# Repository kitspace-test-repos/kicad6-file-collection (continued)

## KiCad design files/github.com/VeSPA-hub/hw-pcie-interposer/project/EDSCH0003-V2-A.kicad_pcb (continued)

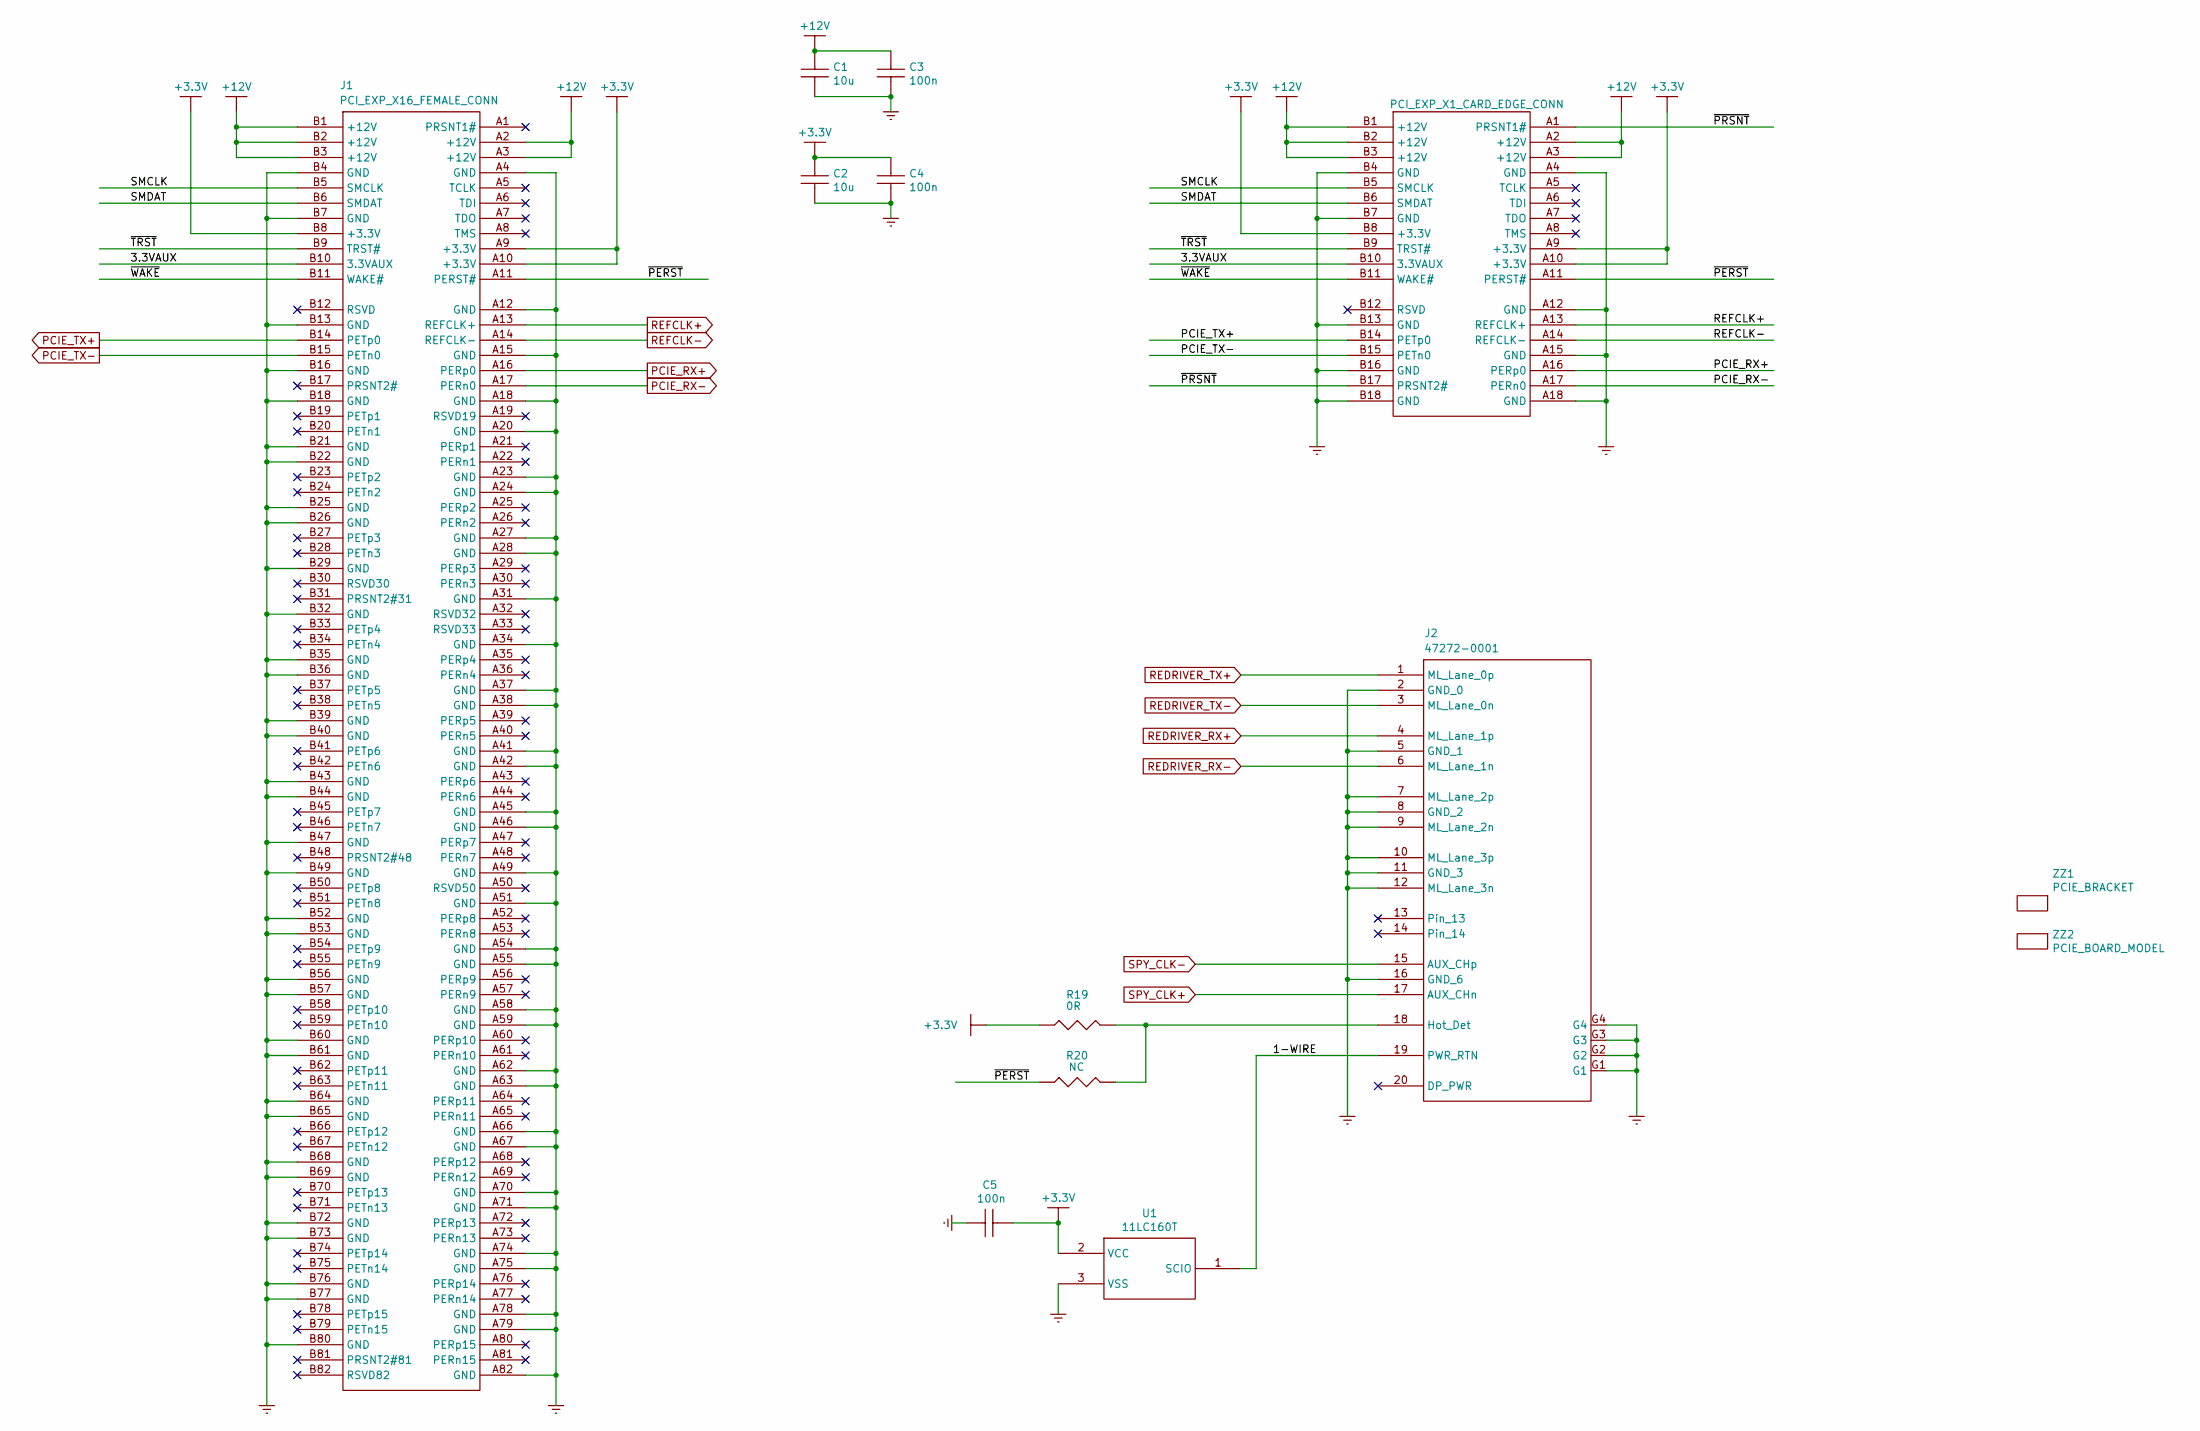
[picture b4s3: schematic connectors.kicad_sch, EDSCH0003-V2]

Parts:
C1, C2: C10U_50V_1206; c_smt1206_ref
C3, C4, C5: C100N_16V_0402; r_smt0402_ref
J1: PCIEXP_X16_EDGE_MOUNT_CONN; samtec_pcie_ems2
J2: DISPLAY_PORT; molex_display_port
P1: PCIEXP_X1_CARD_EDGE; BUS_PCIexpress_x1
R19: R0R_5%_0402; r_smt0402_ref
R20: R_NC_0402; r_smt0402_ref
U1: EEPROM_1WIRE_2Kx8_11LC160T; SOT-23
ZZ1: PCIE_BRACKET; pcie_bracket
ZZ2: PCIE_BOARD_MODEL; BUS_PCIexpress

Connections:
+3.3V: C2.1, C4.1, C5.2, J1.A9 (+3.3V), J1.A10 (+3.3V), J1.B8 (+3.3V), P1.A9 (+3.3V), P1.A10 (+3.3V), P1.B8 (+3.3V), R19.1, U1.2 (VCC); also elsewhere on the board
+12V: C1.1, C3.1, J1.A2 (+12V), J1.A3 (+12V), J1.B1 (+12V), J1.B2 (+12V), J1.B3 (+12V), P1.A2 (+12V), P1.A3 (+12V), P1.B1 (+12V), P1.B2 (+12V), P1.B3 (+12V)
/MASTER_SHEET/CONNECTORS/1-WIRE: J2.19 (PWR_RTN), U1.1 (SCIO)
/MASTER_SHEET/CONNECTORS/3.3VAUX: J1.B10 (3.3VAUX), P1.B10 (3.3VAUX)
/MASTER_SHEET/CONNECTORS/SMCLK: J1.B5 (SMCLK), P1.B5 (SMCLK)
/MASTER_SHEET/CONNECTORS/SMDAT: J1.B6 (SMDAT), P1.B6 (SMDAT)
/MASTER_SHEET/CONNECTORS/~PERST: J1.A11 (PERST#), P1.A11 (PERST#), R20.1
/MASTER_SHEET/CONNECTORS/~PRSNT: P1.A1 (PRSNT1#), P1.B17 (PRSNT2#)
/MASTER_SHEET/CONNECTORS/~TRST: J1.B9 (TRST#), P1.B9 (TRST#)
/MASTER_SHEET/CONNECTORS/~WAKE: J1.B11 (WAKE#), P1.B11 (WAKE#)
GND: C1.2, C2.2, C3.2, C4.2, C5.1, J1.A4 (GND), J1.A12 (GND), J1.A15 (GND), J1.A18 (GND), J1.A20 (GND), J1.A23 (GND), J1.A24 (GND), J1.A27 (GND), J1.A28 (GND), J1.A31 (GND), J1.A34 (GND), J1.A37 (GND), J1.A38 (GND), J1.A41 (GND), J1.A42 (GND), J1.A45 (GND), J1.A46 (GND), J1.A49 (GND), J1.A51 (GND), J1.A54 (GND), J1.A55 (GND), J1.A58 (GND), J1.A59 (GND), J1.A62 (GND), J1.A63 (GND), J1.A66 (GND), J1.A67 (GND), J1.A70 (GND), J1.A71 (GND), J1.A74 (GND), J1.A75 (GND), J1.A78 (GND), J1.A79 (GND), J1.A82 (GND), J1.B4 (GND), J1.B7 (GND), J1.B13 (GND), J1.B16 (GND), J1.B18 (GND), J1.B21 (GND), J1.B22 (GND), J1.B25 (GND), J1.B26 (GND), J1.B29 (GND), J1.B32 (GND), J1.B35 (GND), J1.B36 (GND), J1.B39 (GND), J1.B40 (GND), J1.B43 (GND), J1.B44 (GND), J1.B47 (GND), J1.B49 (GND), J1.B52 (GND), J1.B53 (GND), J1.B56 (GND), J1.B57 (GND), J1.B60 (GND), J1.B61 (GND), J1.B64 (GND), J1.B65 (GND), J1.B68 (GND), J1.B69 (GND), J1.B72 (GND), J1.B73 (GND), J1.B76 (GND), J1.B77 (GND), J1.B80 (GND), J2.2 (GND_0), J2.5 (GND_1), J2.7 (ML_Lane_2p), J2.8 (GND_2), J2.9 (ML_Lane_2n), J2.10 (ML_Lane_3p), J2.11 (GND_3), J2.12 (ML_Lane_3n), J2.16 (GND_6), J2.G1, J2.G2, J2.G3, J2.G4, P1.A4 (GND), P1.A12 (GND), P1.A15 (GND), P1.A18 (GND), P1.B4 (GND), P1.B7 (GND), P1.B13 (GND), P1.B16 (GND), P1.B18 (GND), U1.3 (VSS); also elsewhere on the board
unnamed: J2.18 (Hot_Det), R19.2, R20.2
PCIE_RX+: J1.A16 (PERp0), P1.A16 (PERp0); also elsewhere on the board
PCIE_RX-: J1.A17 (PERn0), P1.A17 (PERn0); also elsewhere on the board
PCIE_TX+: J1.B14 (PETp0), P1.B14 (PETp0); also elsewhere on the board
PCIE_TX-: J1.B15 (PETn0), P1.B15 (PETn0); also elsewhere on the board
REDRIVER_RX+: J2.4 (ML_Lane_1p); also elsewhere on the board
REDRIVER_RX-: J2.6 (ML_Lane_1n); also elsewhere on the board
REDRIVER_TX+: J2.1 (ML_Lane_0p); also elsewhere on the board
REDRIVER_TX-: J2.3 (ML_Lane_0n); also elsewhere on the board
REFCLK+: J1.A13 (REFCLK+), P1.A13 (REFCLK+); also elsewhere on the board
REFCLK-: J1.A14 (REFCLK-), P1.A14 (REFCLK-); also elsewhere on the board
SPY_CLK+: J2.17 (AUX_CHn); also elsewhere on the board
SPY_CLK-: J2.15 (AUX_CHp); also elsewhere on the board

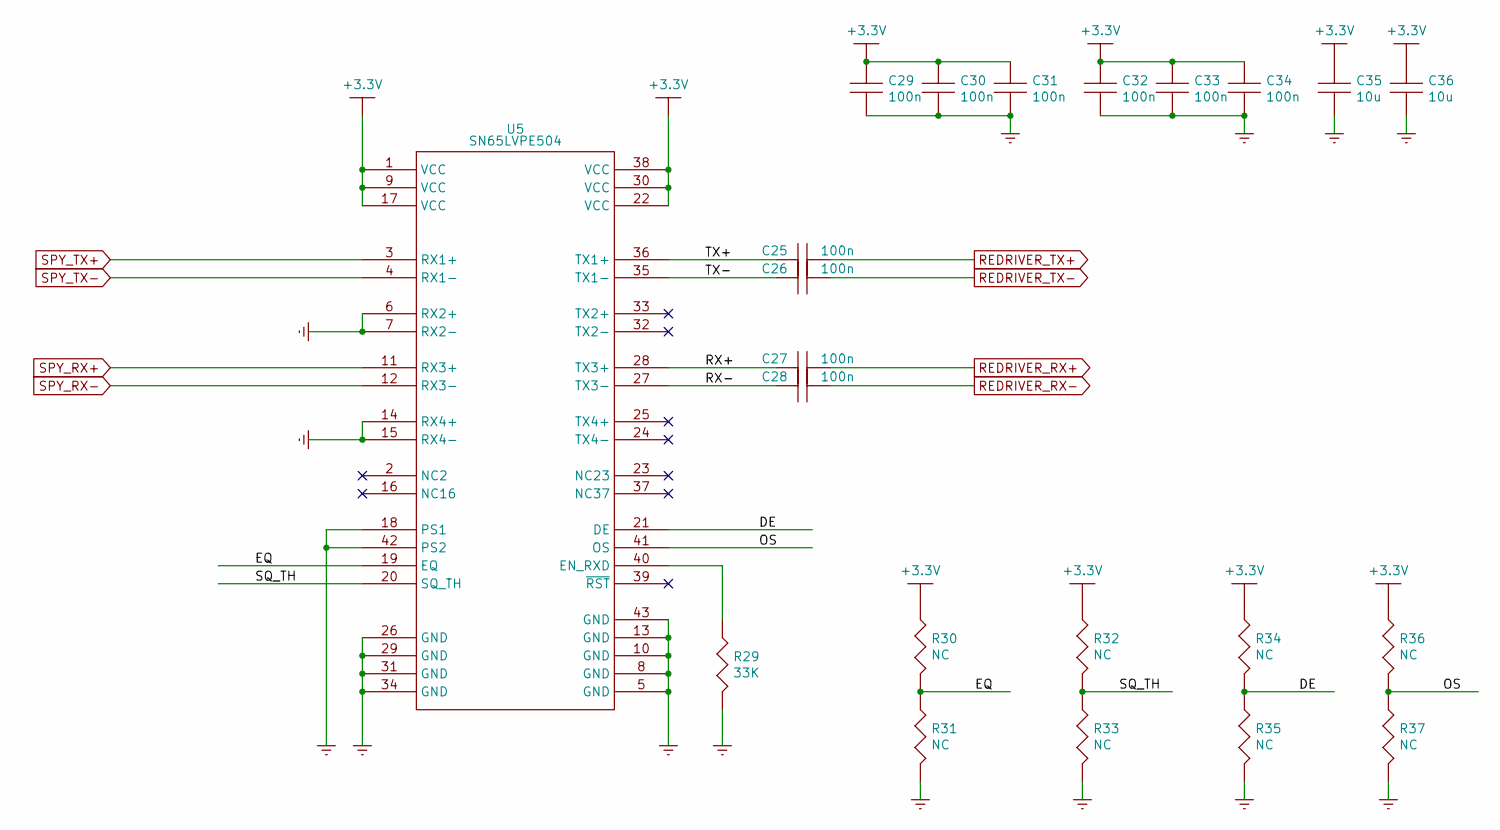
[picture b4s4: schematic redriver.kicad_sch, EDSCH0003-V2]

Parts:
C25, C26, C27, C28, C29, C30, C31, C32, C33, C34: C100N_16V_0402; r_smt0402_ref
C35, C36: C10U_50V_1206; c_smt1206_ref
R29: R33K_1%_0402; r_smt0402_ref
R30, R31, R32, R33, R34, R35, R36, R37: R_NC_0402; r_smt0402_ref
U5: PCIe_HALF_x4_Gen2_SN65LVPE504; pwqfn-n42

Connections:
+3.3V: C29.1, C30.1, C31.1, C32.1, C33.1, C34.1, C35.1, C36.1, R30.1, R32.1, R34.1, R36.1, U5.1 (VCC), U5.9 (VCC), U5.17 (VCC), U5.22 (VCC), U5.30 (VCC), U5.38 (VCC); also elsewhere on the board
/MASTER_SHEET/REDRIVER/DE: R34.2, R35.1, U5.21 (DE)
/MASTER_SHEET/REDRIVER/EQ: R30.2, R31.1, U5.19 (EQ)
/MASTER_SHEET/REDRIVER/OS: R36.2, R37.1, U5.41 (OS)
/MASTER_SHEET/REDRIVER/RX+: C27.1, U5.28 (TX3+)
/MASTER_SHEET/REDRIVER/RX-: C28.1, U5.27 (TX3-)
/MASTER_SHEET/REDRIVER/SQ_TH: R32.2, R33.1, U5.20 (SQ_TH)
/MASTER_SHEET/REDRIVER/TX+: C25.1, U5.36 (TX1+)
/MASTER_SHEET/REDRIVER/TX-: C26.1, U5.35 (TX1-)
GND: C29.2, C30.2, C31.2, C32.2, C33.2, C34.2, C35.2, C36.2, R29.2, R31.2, R33.2, R35.2, R37.2, U5.5 (GND), U5.6 (RX2+), U5.7 (RX2-), U5.8 (GND), U5.10 (GND), U5.13 (GND), U5.14 (RX4+), U5.15 (RX4-), U5.18 (PS1), U5.26 (GND), U5.29 (GND), U5.31 (GND), U5.34 (GND), U5.42 (PS2), U5.43 (GND); also elsewhere on the board
unnamed: R29.1, U5.40 (EN_RXD)
REDRIVER_RX+: C27.2; also elsewhere on the board
REDRIVER_RX-: C28.2; also elsewhere on the board
REDRIVER_TX+: C25.2; also elsewhere on the board
REDRIVER_TX-: C26.2; also elsewhere on the board
SPY_RX+: U5.11 (RX3+); also elsewhere on the board
SPY_RX-: U5.12 (RX3-); also elsewhere on the board
SPY_TX+: U5.3 (RX1+); also elsewhere on the board
SPY_TX-: U5.4 (RX1-); also elsewhere on the board

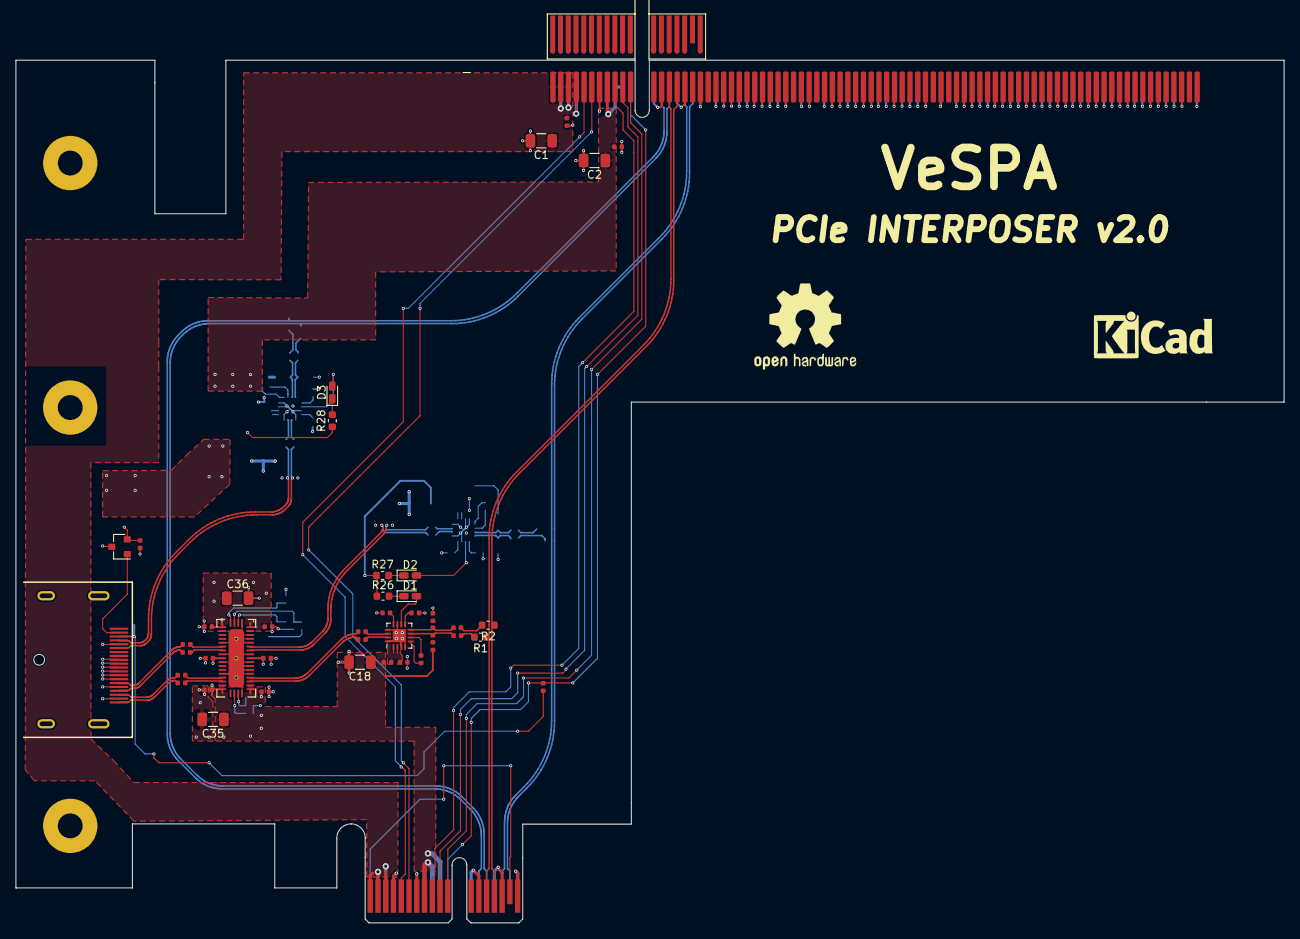
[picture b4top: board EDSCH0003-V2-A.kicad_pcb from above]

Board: 4 copper layers, 163.4 x 111.2 mm, 89 parts (0 on the bottom side), 76 nets.

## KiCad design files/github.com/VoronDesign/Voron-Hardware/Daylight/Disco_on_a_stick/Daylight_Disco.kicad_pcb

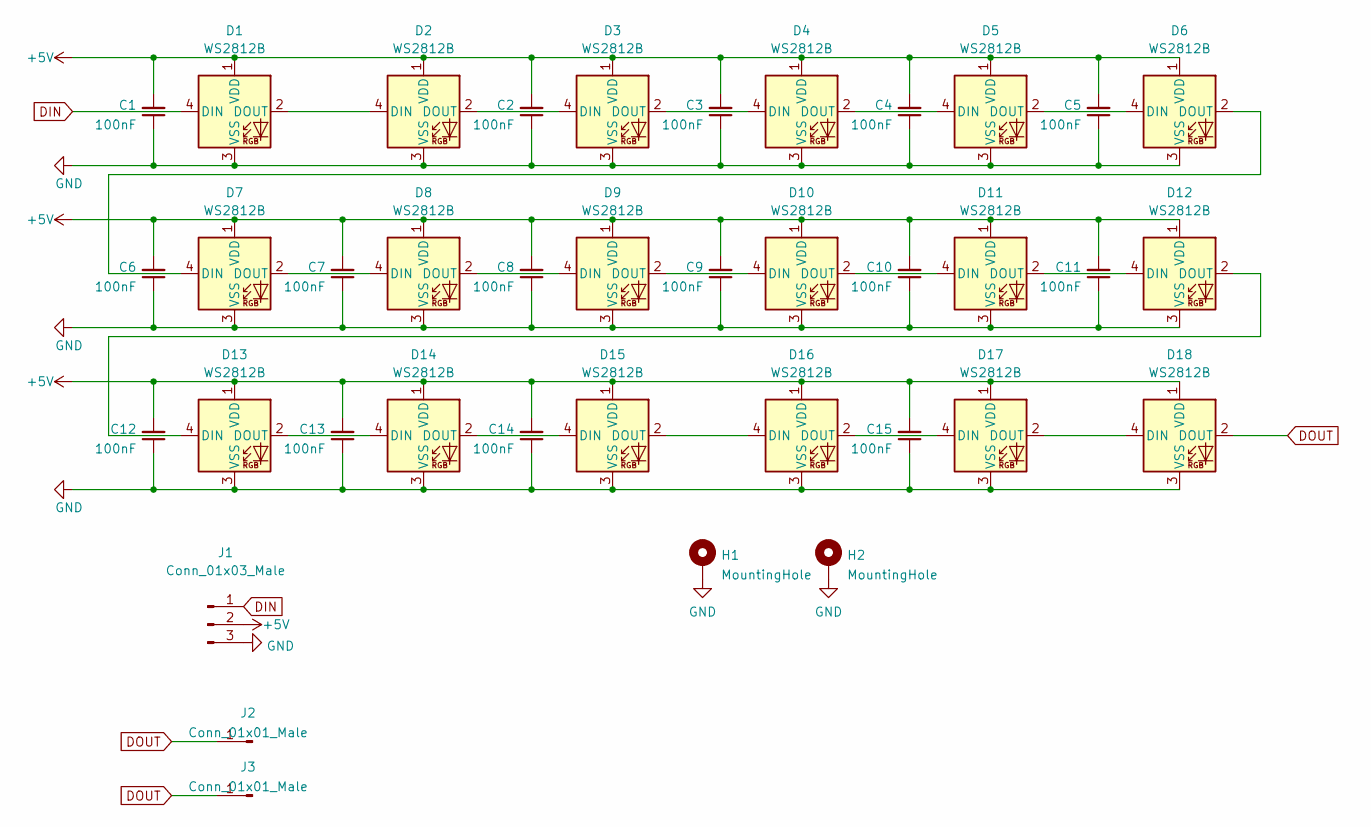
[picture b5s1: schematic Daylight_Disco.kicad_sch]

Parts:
C1, C2, C3, C4, C5, C6, C7, C8, C9, C10, C11, C12, C13, C14, C15: 100nF; C_0805_2012Metric_Pad1.18x1.45mm_HandSolder
D1, D2, D3, D4, D5, D6, D7, D8, D9, D10, D11, D12, D13, D14, D15, D16, D17, D18: WS2812B; LED_WS2812B_PLCC4_5.0x5.0mm_P3.2mm
H1, H2: MountingHole; MountingHole_3.2mm_M3_Pad_Via
J1: Conn_01x03_Male; JST_XH_S3B-XH-A-1_1x03_P2.50mm_Horizontal
J2, J3: Conn_01x01_Male; PinHeader-1-with-SMDpad

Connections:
+5V: C1.2, C2.2, C3.2, C4.2, C5.2, C6.2, C7.2, C8.2, C9.2, C10.2, C11.2, C12.2, C13.2, C14.2, C15.2, D1.1 (VDD), D2.1 (VDD), D3.1 (VDD), D4.1 (VDD), D5.1 (VDD), D6.1 (VDD), D7.1 (VDD), D8.1 (VDD), D9.1 (VDD), D10.1 (VDD), D11.1 (VDD), D12.1 (VDD), D13.1 (VDD), D14.1 (VDD), D15.1 (VDD), D16.1 (VDD), D17.1 (VDD), D18.1 (VDD), J1.2
DIN: D1.4 (DIN), J1.1
DOUT: D18.2 (DOUT), J2.1, J3.1
GND: C1.1, C2.1, C3.1, C4.1, C5.1, C6.1, C7.1, C8.1, C9.1, C10.1, C11.1, C12.1, C13.1, C14.1, C15.1, D1.3 (VSS), D2.3 (VSS), D3.3 (VSS), D4.3 (VSS), D5.3 (VSS), D6.3 (VSS), D7.3 (VSS), D8.3 (VSS), D9.3 (VSS), D10.3 (VSS), D11.3 (VSS), D12.3 (VSS), D13.3 (VSS), D14.3 (VSS), D15.3 (VSS), D16.3 (VSS), D17.3 (VSS), D18.3 (VSS), H1.1, H2.1, J1.3
unnamed: D1.2 (DOUT), D2.4 (DIN)
unnamed: D2.2 (DOUT), D3.4 (DIN)
unnamed: D3.2 (DOUT), D4.4 (DIN)
unnamed: D4.2 (DOUT), D5.4 (DIN)
unnamed: D5.2 (DOUT), D6.4 (DIN)
unnamed: D6.2 (DOUT), D7.4 (DIN)
unnamed: D7.2 (DOUT), D8.4 (DIN)
unnamed: D8.2 (DOUT), D9.4 (DIN)
unnamed: D10.2 (DOUT), D11.4 (DIN)
unnamed: D9.2 (DOUT), D10.4 (DIN)
unnamed: D11.2 (DOUT), D12.4 (DIN)
unnamed: D12.2 (DOUT), D13.4 (DIN)
unnamed: D13.2 (DOUT), D14.4 (DIN)
unnamed: D14.2 (DOUT), D15.4 (DIN)
unnamed: D15.2 (DOUT), D16.4 (DIN)
unnamed: D16.2 (DOUT), D17.4 (DIN)
unnamed: D17.2 (DOUT), D18.4 (DIN)

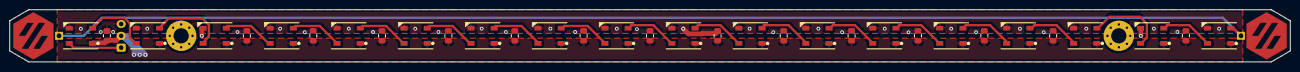
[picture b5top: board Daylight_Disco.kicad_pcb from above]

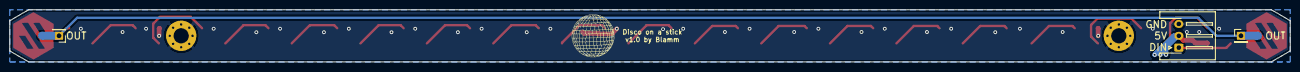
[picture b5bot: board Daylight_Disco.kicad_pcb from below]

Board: 2 copper layers, 270.0 x 11.0 mm, 38 parts (3 on the bottom side), 21 nets.

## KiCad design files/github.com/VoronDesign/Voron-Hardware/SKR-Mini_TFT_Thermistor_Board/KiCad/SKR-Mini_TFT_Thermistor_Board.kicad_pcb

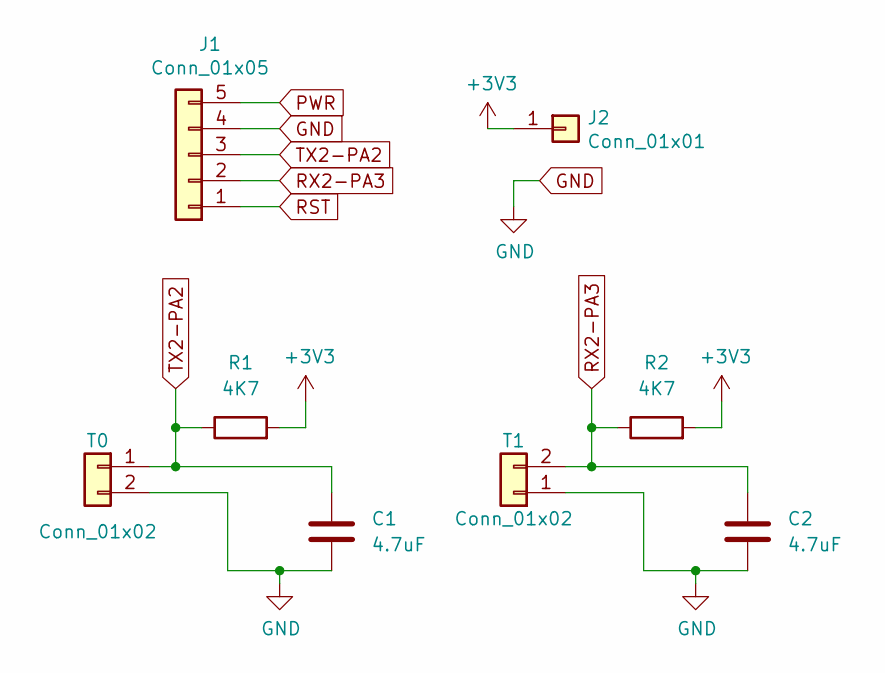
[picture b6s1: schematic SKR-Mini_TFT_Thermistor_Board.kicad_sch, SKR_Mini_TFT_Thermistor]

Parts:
C1, C2: 4.7uF; C_0805_2012Metric_Pad1.18x1.45mm_HandSolder
J1: Conn_01x05; PinSocket_1x05_P2.54mm_Vertical
J2: Conn_01x01; PinHeader_1x01_P2.54mm_Vertical
R1, R2: 4K7; R_0805_2012Metric_Pad1.20x1.40mm_HandSolder
T0, T1: Conn_01x02; JST_XH_B2B-XH-A_1x02_P2.50mm_Vertical

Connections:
+3V3: J2.1, R1.2, R2.2
GND: C1.2, C2.2, J1.4, T0.2, T1.1
PWR: J1.5
RST: J1.1
RX2-PA3: C2.1, J1.2, R2.1, T1.2
TX2-PA2: C1.1, J1.3, R1.1, T0.1

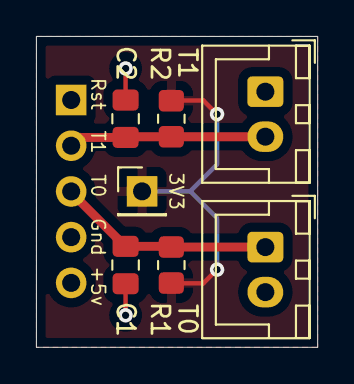
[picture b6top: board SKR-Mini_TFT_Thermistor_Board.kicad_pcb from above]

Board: 2 copper layers, 15.6 x 17.3 mm, 8 parts (1 on the bottom side), 4 nets.
